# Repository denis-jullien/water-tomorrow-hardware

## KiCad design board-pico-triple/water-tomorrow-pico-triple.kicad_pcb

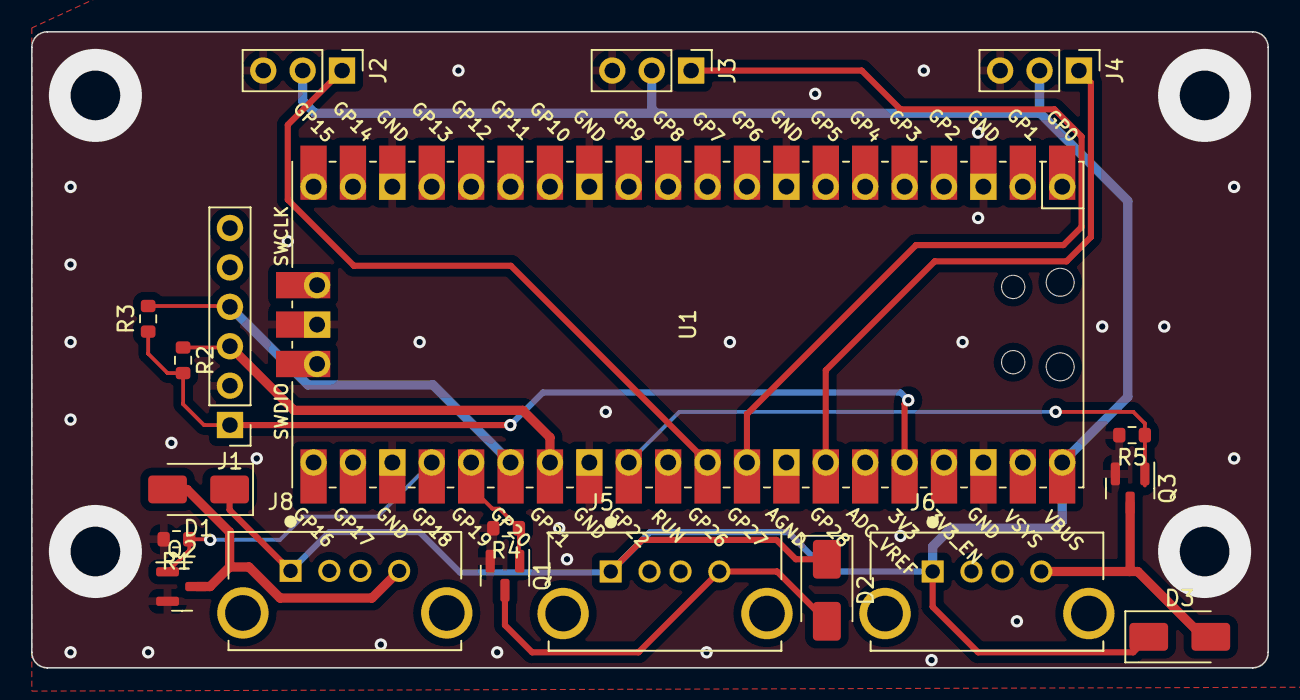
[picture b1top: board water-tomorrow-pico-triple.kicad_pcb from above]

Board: 2 copper layers, 79.7 x 41.0 mm, 19 parts (0 on the bottom side), 14 nets.

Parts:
D1, D2, D3: SS34; D_SMA
J1: Conn_01x06; PinHeader_1x06_P2.54mm_Vertical
J2, J3, J4: Conn_01x03; PinHeader_1x03_P2.54mm_Vertical
J5, J6, J8: USB_A; TE_1734366-1
Q1, Q2, Q3: AO3400A; SOT-23
R1, R2, R3, R4, R5: 10k; R_0603_1608Metric
U1: Pico; RPi_Pico_SMD_TH

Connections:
+3.3V: J1.1, R2.2, R3.1, U1.36 (3V3)
/ADC0: J2.1, U1.31 (GPIO26_ADC0)
/ADC1: J3.1, U1.32 (GPIO27_ADC1)
/ADC2: J4.1, U1.34 (GPIO28_ADC2)
/PWM_M0: Q2.1 (G), R1.1, U1.24 (GPIO18)
/PWM_M1: Q1.1 (G), R4.1, U1.25 (GPIO19)
/PWM_M2: Q3.1 (G), R5.1, U1.29 (GPIO22)
/SCL: J1.3, R2.1, U1.27 (GPIO21)
/SDA: J1.4, R3.2, U1.26 (GPIO20)
GND: J1.2, J2.3, J3.3, J4.3, Q1.2 (S), Q2.2 (S), Q3.2 (S), R1.2, R4.2, R5.2, U1.3 (GND), U1.8 (GND), U1.13 (GND), U1.18 (GND), U1.23 (GND), U1.28 (GND), U1.38 (GND), U1.42 (GND)
unnamed: D1.2 (A), J8.4 (GND), Q2.3 (D)
unnamed: D2.2 (A), J5.4 (GND), Q1.3 (D)
unnamed: D3.2 (A), J6.4 (GND), Q3.3 (D)
VDC: D1.1 (K), D2.1 (K), D3.1 (K), J2.2, J3.2, J4.2, J5.1 (VBUS), J6.1 (VBUS), J8.1 (VBUS), U1.40 (VBUS)

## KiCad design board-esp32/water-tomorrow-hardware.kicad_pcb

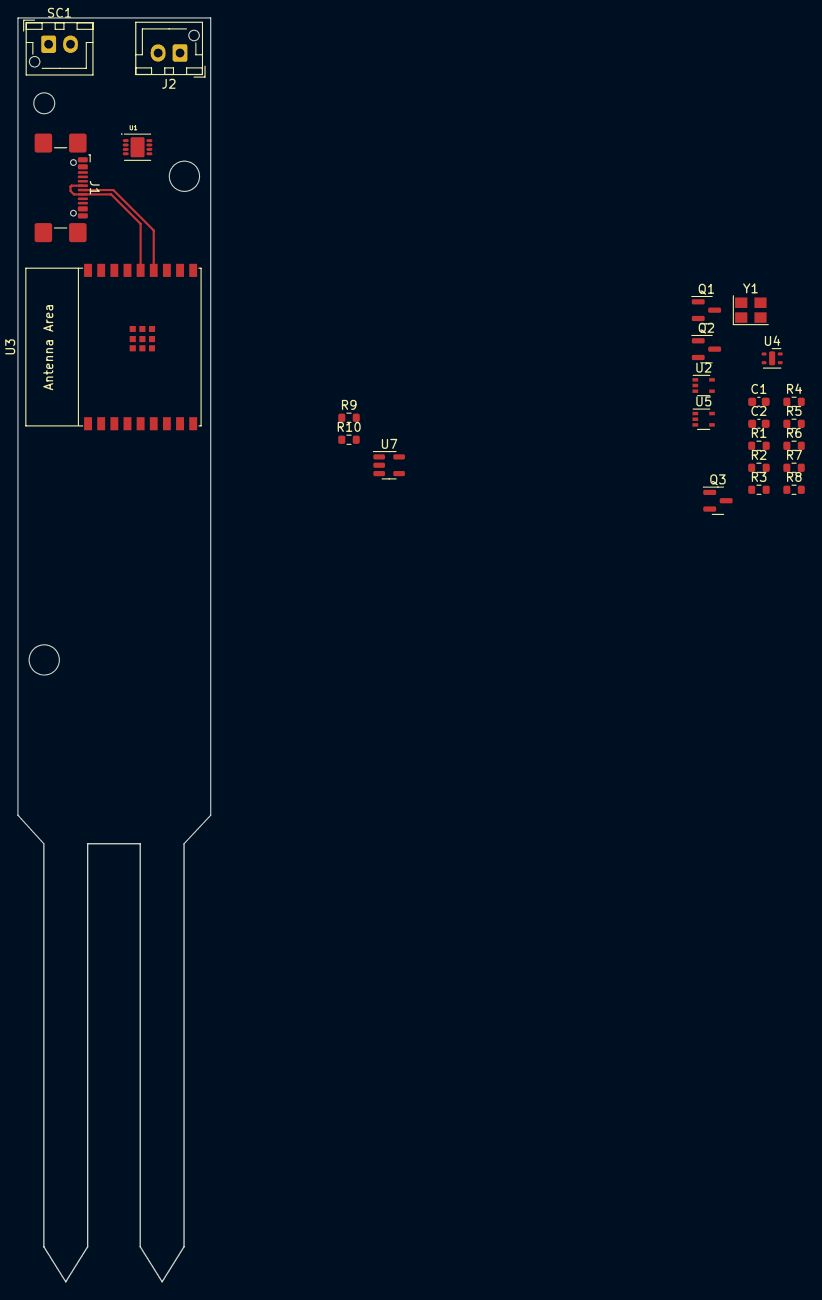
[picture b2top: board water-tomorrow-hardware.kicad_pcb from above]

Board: 2 copper layers, 22.0 x 144.2 mm, 26 parts (1 on the bottom side), 20 nets.

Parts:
BT1: Battery_Cell; BatteryHolder_Keystone_1042_1x18650
C1, C2: 18p; C_0603_1608Metric
J1: USB_C_Receptacle_USB2.0; USB_C_Receptacle_GCT_USB4110
J2: Conn_01x02; JST_XH_B2B-XH-AM_1x02_P2.50mm_Vertical
Q1, Q2, Q3: AO3401A; SOT-23
R1, R2, R3, R5, R6, R7, R8, R9, R10: 10k; R_0603_1608Metric
R4: R_0603_1608Metric
SC1: Solar_Cells; JST_XH_B2B-XH-AM_1x02_P2.50mm_Vertical
U1: CN3165; DFN300X300X90-9N
U2, U5: 74LVC1G86; SOT-353_SC-70-5
U3: ESP32-C3-WROOM-02
U4: SHTC3; Sensirion_DFN-4-1EP_2x2mm_P1mm_EP0.7x1.6mm
U7: RT9080-33GJ5; TSOT-23-5
Y1: 32.768k; Crystal_SMD_3225-4Pin_3.2x2.5mm

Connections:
+3.3V: Q2.3 (D), R3.1, R5.2, R6.1, R7.2, U3.1 (3V3), U4.1 (VDD), U7.5 (VOUT)
+BATT: BT1.1 (+), Q1.3 (D), R8.2, U1.5 (BAT), U1.8 (FB), U7.1 (VIN), U7.3 (EN)
GND: BT1.2 (-), C1.2, C2.2, J1.A1 (GND), J1.A12 (GND), J1.B1 (GND), J1.B12 (GND), J1.S1 (SHIELD), J2.2, R4.1, R10.1, SC1.2 (-), U1.1 (TEMP), U1.3 (GND), U2.3 (GND), U3.9 (GND), U3.19 (GND), U4.4 (VSS), U5.2, U5.3 (GND), U7.2 (GND), Y1.2, Y1.4
unnamed: Q3.2 (S), U1.4 (VIN)
unnamed: J1.A5 (CC1), R2.2
unnamed: J1.B5 (CC2), R1.1
unnamed: J2.1, Q1.2 (S)
unnamed: Q1.1 (G), R8.1
unnamed: Q2.1 (G), R7.1
unnamed: Q2.2 (S), U2.5 (VCC), U5.5 (VCC)
unnamed: Q3.3 (D), SC1.1 (+)
unnamed: R4.2, U1.2 (ISET)
unnamed: R3.2, U3.2 (EN/CHIP_PU)
unnamed: C1.1, U3.18 (GPIO0/ADC1_CH0/XTAL_32K_P), Y1.1
unnamed: C2.1, U3.17 (GPIO1/ADC1_CH1/XTAL_32K_N), Y1.3
unnamed: J1.A7 (D-), J1.B7 (D-), U3.13 (GPIO18/USB_D-)
unnamed: J1.A6 (D+), J1.B6 (D+), U3.14 (GPIO19/USB_D+)
unnamed: R6.2, U4.2 (SCL)
unnamed: R5.1, U4.3 (SDA)
VDC: J1.A4 (VBUS), J1.A9 (VBUS), J1.B4 (VBUS), J1.B9 (VBUS), Q3.1 (G), R1.2, R2.1, R9.2, R10.2

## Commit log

2023-12-14 Init pico-triple board for protype
